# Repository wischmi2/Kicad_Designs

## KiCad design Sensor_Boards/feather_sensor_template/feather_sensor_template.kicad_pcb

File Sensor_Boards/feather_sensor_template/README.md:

# Feather sensor board template

KiCad 10 template for sensor boards that stack under the nRF54L15 feather. Each node is one feather plus one sensor board in its own enclosure (pH node, salinity node, ...). The two boards are joined by a 14-way 0.5 mm FFC between the two CN1 connectors; the R_ID resistor on the sensor board tells the firmware which board is fitted.

Derived from nrf54l15_feather_sens1 (pH) on 2026-10-25. Current numbers and open questions: STATUS.md.

## What is in the template

| Sheet | Contents | Change per board? |
|---|---|---|
| Sensor Connector | CN1 Molex 503480-1400, C1 1 uF + C2 100 nF on VSENS, R1 = R_ID (SENS_ID to GND) | Only R1's value |
| Isolation | U3 ADuM1250 I2C isolator, U4 NXE1S0303MC isolated DC-DC, C3, C4, R3/R4 4.7k isolated-side pull-ups, J5 INT_ISO test pad | Normally no. Delete it for a non-isolated board |
| Sensor | Empty. Hierarchical labels VDD_ISO, GND_ISO, SDA_ISO, SCL_ISO, INT_ISO | Yes, the sensor circuit goes here |

PCB (origin = outline top-left corner at (90, 110), the same as the feather):
- Outline 50.8 x 22.86 mm, R2.54 corners, 4 layers, same stackup, design rules and net classes as sens1.
- CN1 at (138.475, 121.43), rotation 90, pin 1 at (137.15, 124.68): exactly under the feather's CN1.
- Isolation barrier at x = 124: isolated pours (GND_ISO) end at x 122.5, host pours (GND) start at x 125.5, rule area ISOLATION_BARRIER in between on all 4 layers.
- Sensor placement area: x 90 to about 116 (isolated side), outlined on Dwgs.User. GND_ISO pours already on all 4 layers.
- Antenna-corner keep-out ANTENNA_CORNER_keepout: x 132.15 to 140.8, y 126.40 to 132.86, all copper layers, no tracks, vias or pours. It is the feather's antenna keep-out copied 1:1; the feather's chip antenna sits right above it.
- Holes at the Feather positions, 2.7 mm drill: H1 (92.54, 112.54) and H2 (92.54, 130.32) NPTH with 3.5 mm keep-outs (isolated end); H3 (138.26, 112.54) plated GND; H4 (138.26, 130.32) NPTH (inside the antenna keep-out).

## Starting a new sensor board

1. **Copy the project.** Open feather_sensor_template.kicad_pro in the KiCad project manager and use File > Save As to a new folder under Sensor_Boards (for example Sensor_Boards\feather_sens2_salinity\feather_sens2_salinity). KiCad renames the project files and keeps the sheet instances working.
   - Fallback by hand: copy the folder (skip any `~*.lck` files), rename the four `feather_sensor_template.kicad_*` files to the new name, and replace the project name inside them: `sed -i 's/"feather_sensor_template"/"<new_name>"/g' *.kicad_sch *.kicad_pro`. The footprint library nickname `feather_sensor_template` (fp-lib-table and the .pretty folder) can stay as it is.
   - Never edit the template itself for a real board.
2. **Set R_ID.** Pick the next free board type in the ID table (v4-sensor-connector.md, "Board ID - pin 11"; the R1 value field says "set per SENSORS.md", the ID register) and set R1's value to it on the Sensor Connector sheet, 1 % tolerance. Update the "SENSOR TYPE / R_ID" text on B.SilkS and record the assignment in the ID table.
3. **Fill the Sensor sheet.** Draw the sensor circuit on sensor.kicad_sch and connect it to the hierarchical labels. Delete the short wire stubs on the labels as you wire them (they only exist so the empty template passes ERC). Place new symbols in the KiCad GUI.
4. **Update the PCB** (Tools > Update PCB from Schematic), place the new parts in the sensor area, put the probe connector on the x = 90 short edge (opposite CN1, so the probe cable leaves the other end of the enclosure), route, refill the zones.
5. **Rename the board.** Title blocks on all sheets, "FEATHER SENSOR <NAME> rev" on B.SilkS, and a STATUS.md for the new board.
6. **Check.** `kicad-cli sch erc` (0 errors) and `kicad-cli pcb drc --schematic-parity --refill-zones` (0 errors, 0 unconnected, 0 parity). Export a STEP to C:\Personal-Agents\shared\handoff\<project>\ for the enclosure.

## Fixed: do not move or change

- **Outline, hole positions and origin.** The boards stack 1:1 on shared standoffs.
- **CN1**: footprint, position (138.475, 121.43), rotation 90 and pinout. Moving it breaks the straight FFC fold and the pin-1-to-pin-1 mapping.
- **Antenna-corner keep-out** under the feather's chip antenna: no copper of any kind there (no pours, tracks, vias, and no parts).
- **H1/H2 NPTH keep-outs** on an isolated board: no copper within 3.5 mm of those holes.
- **Barrier**: nothing crosses x 122.5 to 125.5 on any layer except the isolator and DC-DC packages themselves.
- All parts on the top side. The bottom stays flat (silk only), because it faces nothing and the stack height is set by the tallest top-side part.

## Sensor-board rules (from v4-sensor-connector.md)

1. Pin 1 at the same end on every board; print the FFC type on the silkscreen. For the U-folded cable the contacts end up on opposite faces at the two ends (opposite-side FFC); the 503480 is dual contact, so a same-side cable also works.
2. No I2C pull-ups on the host side of the sensor board. The feather has 4.7k to VSENS on SDA/SCL and 10k on CS and INT. (The isolated side needs its own: R3/R4 in the template.)
3. Fit the ID resistor (pin 11 to GND), 1 %.
4. Run logic from VSENS (switched 3.0 V, 100 mA max, shared with the feather's BUCK2). Use VBAT (pin 13) only for loads VSENS can't carry, behind a local regulator with an enable and sub-uA shutdown.
5. An analog output on pin 10 (AIN) must be buffered and stay within 0 to 3.0 V. It cannot cross the isolation barrier without extra parts.
6. INT (pin 9) is open-drain, active low.
7. All signals are 3.0 V logic. Before VSENS is switched off, firmware sets every CN1 signal to input or low so nothing back-powers the sensor.
8. Pin usage: I2C on 3/4; SPI on 5 to 8; UART on 6/7; SPI and UART can't be combined (shared instance). Leave unused CN1 pins unconnected.

## Isolated (default) vs non-isolated

**Isolated** (Atlas-style probes in a shared tank: pH, ORP, conductivity, DO). Keep the Isolation sheet. The sensor uses VDD_ISO / GND_ISO / SDA_ISO / SCL_ISO only, and the probe connector shell goes to GND_ISO, never host GND.
- INT_ISO only reaches the J5 test pad: the ADuM1250 has two channels (SDA, SCL). For a host interrupt use a 3-channel isolator or poll.
- VDD_ISO is the unregulated NXE1S0303MC output fed from VSENS (about 3.0 to 3.3 V, and it shares the 100 mA VSENS budget). Check it against the sensor's supply range and current. A sensor that needs a regulated or higher rail (for example EZO-EC, 3.3 V min) needs a different isolated supply, such as the VBAT-fed SN6505 + transformer + LDO in sensor-board-conductivity.md.
- Conformal-coat the isolated side; salt air across the gap defeats the isolation.
- **Nylon standoffs and screws at the isolated end (H1/H2) are mandatory.** The feather's H1/H2 (USB end) are plated and tied to feather GND and sit directly above this board's isolated end; metal hardware there would connect feather GND to the probe side. H4 is nylon too (antenna corner). H3 can be metal.

**Non-isolated** (sealed digital sensors that don't touch the water: temperature/humidity, light, pressure, sealed 1-Wire probes):
1. Delete the Isolation sheet (U3, U4, C3, C4, R3, R4, J5) from the root schematic.
2. On the root sheet, change the five global labels on the Sensor sheet pins to the host nets: VDD_ISO to VSENS, GND_ISO to GND, SDA_ISO to SENS_SDA, SCL_ISO to SENS_SCL, INT_ISO to SENS_INT (or rename the hierarchical labels). Keep C1, C2 and R1.
3. Do not add I2C pull-ups (the host has them).
4. On the PCB: delete the ISOLATION_BARRIER rule area and the GND_ISO zones, and stretch the GND zones over the whole board (keep the antenna-corner keep-out). The H1/H2 NPTH keep-outs can go; H1/H2 can be made plated GND if the board needs the extra ground.
5. Remove "ISOLATED SIDE: NYLON STANDOFFS ONLY" from B.SilkS.

## Files

- feather_sensor_template.kicad_pro / .kicad_sch / .kicad_pcb: project, root sheet, board.
- sensor_connector.kicad_sch, isolation.kicad_sch, sensor.kicad_sch: sub-sheets.
- feather_sensor_template.pretty: CN1 footprint (Molex_503480-1400_1x14-1MP_P0.50mm_Horizontal). 5034801400_0.stp: its 3D model (${KIPRJMOD}).
- The EasyEDA passives use the easyeda2kicad library, which isn't registered on this PC yet (library warnings in ERC/DRC, and no 3D bodies for them in STEP exports).

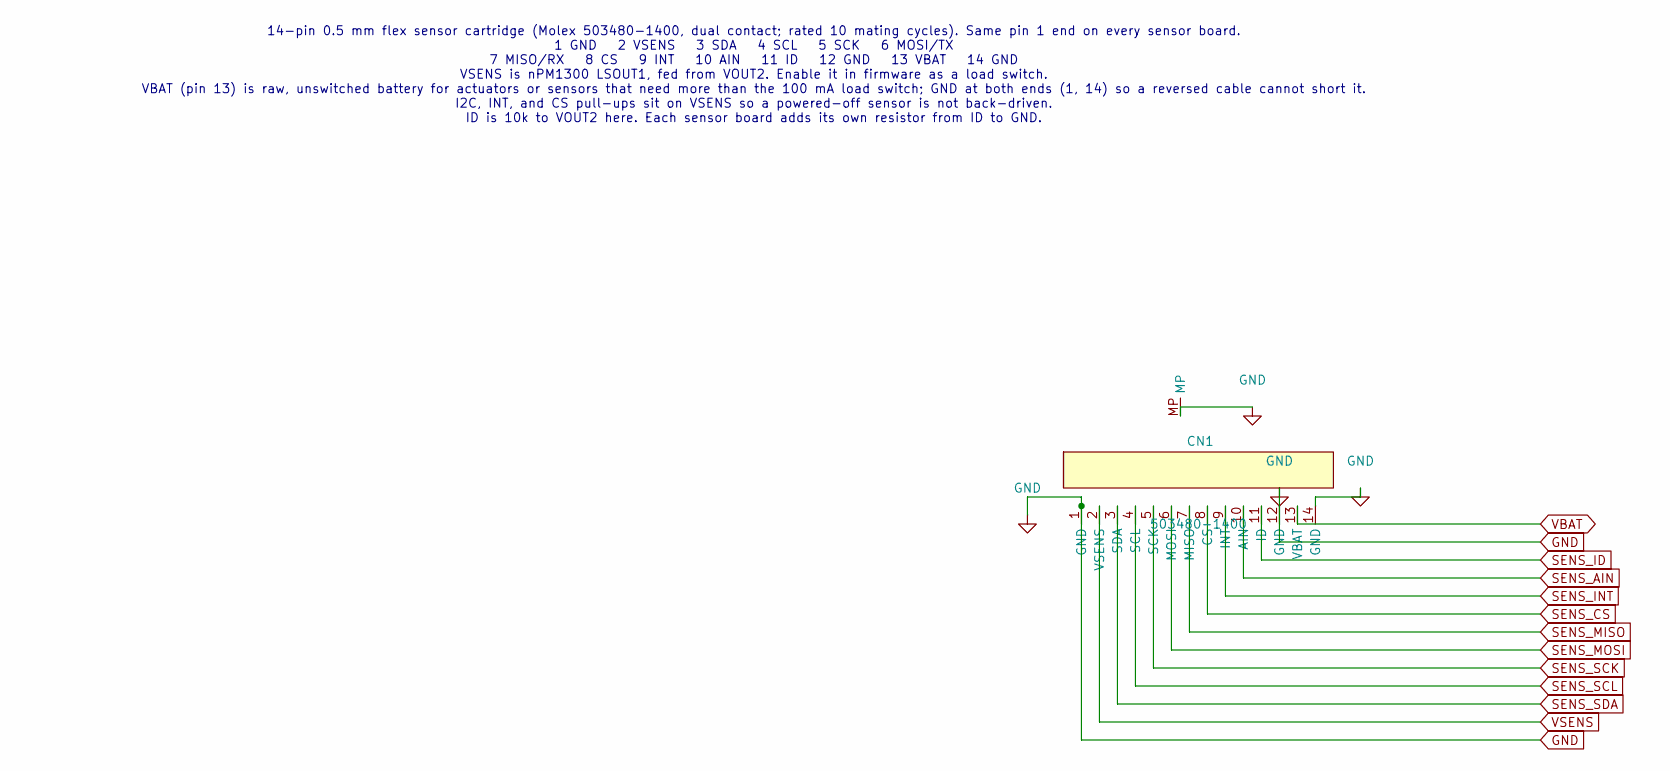
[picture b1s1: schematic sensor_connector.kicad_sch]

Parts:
CN1: 503480-1400; Molex_503480-1400_1x14-1MP_P0.50mm_Horizontal; MPN 503480-1400

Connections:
GND: CN1.1 (GND), CN1.12 (GND), CN1.14 (GND), CN1.MP; also elsewhere on the board
SENS_AIN: CN1.10 (AIN)
SENS_CS: CN1.8 (CS)
SENS_ID: CN1.11 (ID); also elsewhere on the board
SENS_INT: CN1.9 (INT)
SENS_MISO: CN1.7 (MISO)
SENS_MOSI: CN1.6 (MOSI)
SENS_SCK: CN1.5 (SCK)
SENS_SCL: CN1.4 (SCL); also elsewhere on the board
SENS_SDA: CN1.3 (SDA); also elsewhere on the board
VBAT: CN1.13 (VBAT)
VSENS: CN1.2 (VSENS); also elsewhere on the board

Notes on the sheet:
14-pin 0.5 mm flex sensor cartridge (Molex 503480-1400, dual contact; rated 10 mating cycles). Same pin 1 end on every sensor board. 1 GND 2 VSENS 3 SDA 4 SCL 5 SCK 6 MOSI/TX 7 MISO/RX 8 CS 9 INT 10 AIN 11 ID 12 GND 13 VBAT 14 GND VSENS is nPM1300 LSOUT1, fed from VOUT2. Enable it in firmware as a 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

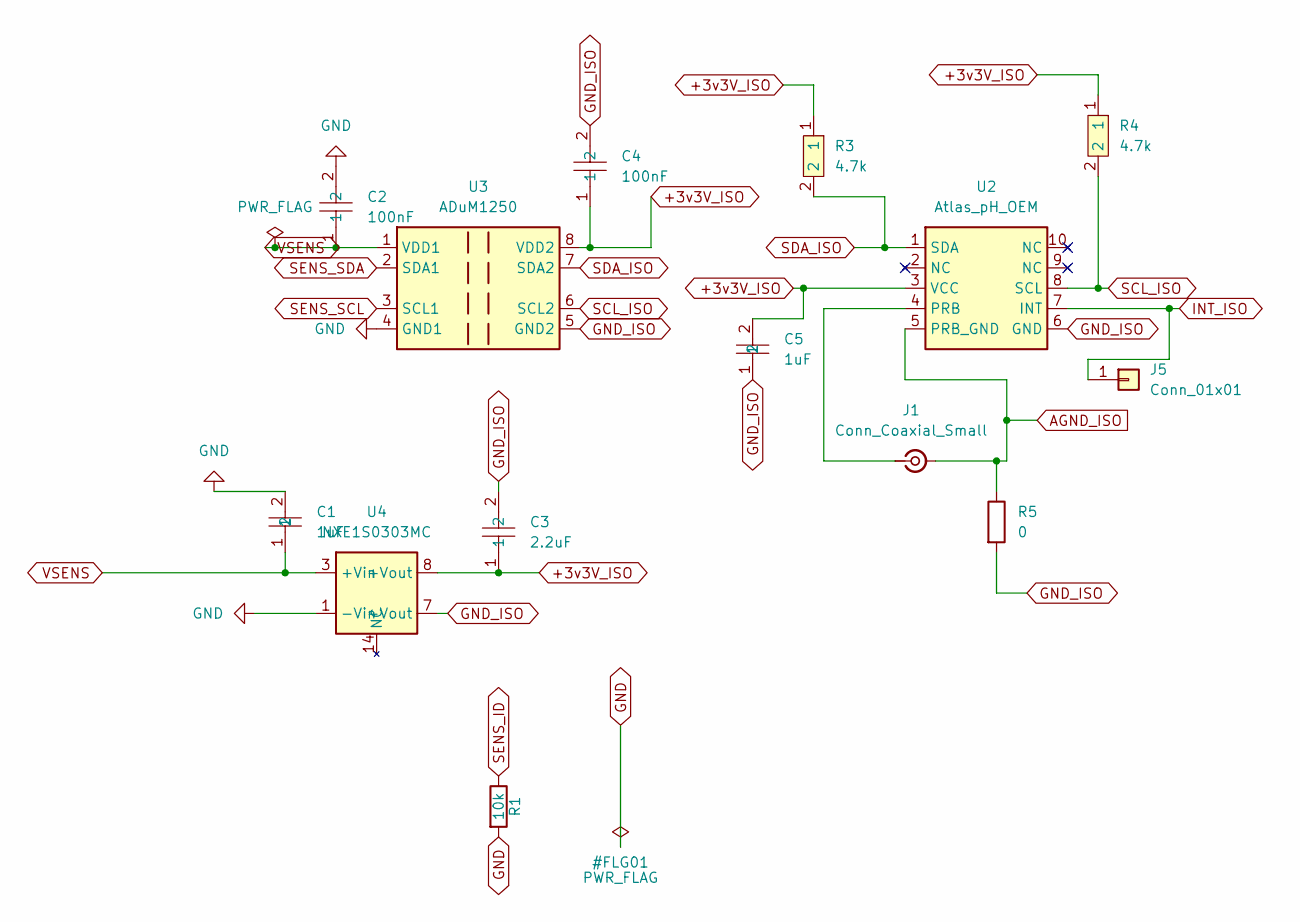
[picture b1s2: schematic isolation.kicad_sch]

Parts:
C1, C5: 1uF; C0402; MPN CL05A105KO5NNNC; LCSC Part C29266
C2, C4: 100nF; C0603; MPN CC0603KRX7R9BB104; LCSC Part C14663
C3: 2.2uF; C0603; MPN GRM188R71A225KE15D; LCSC Part C86018
J1: Conn_Coaxial_Small; SMA_BAT_Wireless_BWSMA-KWE-Z001
J5: Conn_01x01; TestPoint_Pad_D1.0mm
R1: 10k; R0402
R3, R4: 4.7k; R0402; MPN CRCW04024K70FKED; LCSC Part C482193
R5: 0; R0402
U2: Atlas_pH_OEM
U3: ADuM1250; SOIC-8_3.9x4.9mm_P1.27mm
U4: NXE1S0303MC; Converter_DCDC_Murata_NXExSxxxxMC_SMD

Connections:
+3v3V_ISO: C3.1, C4.1, C5.2, R3.1, R4.1, U2.3 (VCC), U3.8 (VDD2), U4.8 (+Vout)
AGND_ISO: J1.2 (Ext), R5.1, U2.5 (PRB_GND)
GND: C1.2, C2.2, R1.2, U3.4 (GND1), U4.1 (-Vin); also elsewhere on the board
GND_ISO: C3.2, C4.2, C5.1, R5.2, U2.6 (GND), U3.5 (GND2), U4.7 (-Vout)
INT_ISO: J5.1 (Pin_1_1), U2.7 (INT)
unnamed: J1.1 (In), U2.4 (PRB)
SCL_ISO: R4.2, U2.8 (SCL), U3.6 (SCL2)
SDA_ISO: R3.2, U2.1 (SDA), U3.7 (SDA2)
SENS_ID: R1.1; also elsewhere on the board
SENS_SCL: U3.3 (SCL1); also elsewhere on the board
SENS_SDA: U3.2 (SDA1); also elsewhere on the board
VSENS: C1.1, C2.1, U3.1 (VDD1), U4.3 (+Vin); also elsewhere on the board

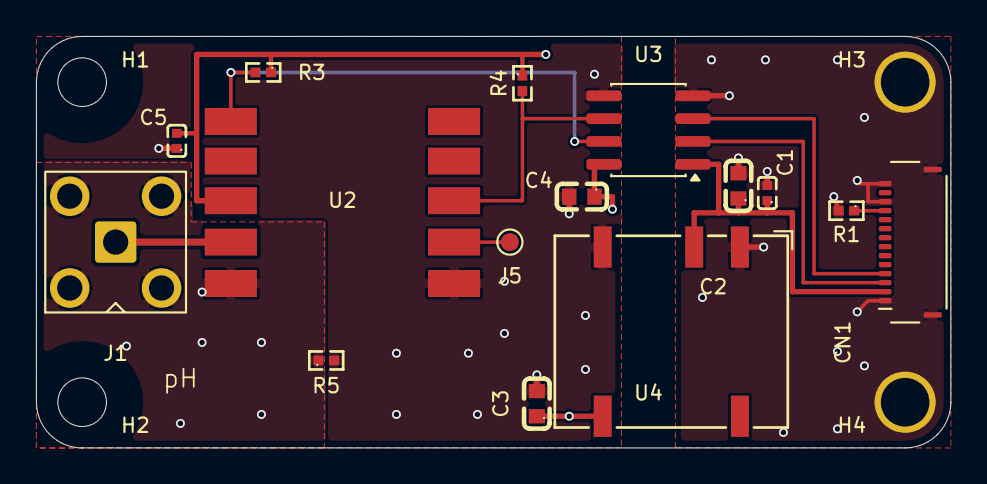
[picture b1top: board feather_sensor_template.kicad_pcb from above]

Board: 4 copper layers, 50.8 x 22.9 mm, 19 parts (0 on the bottom side), 12 nets.

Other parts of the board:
H1, H2: M2.5 2.7mm NPTH; MountingHole_2.5mm
H3, H4: M2.5 2.7mm PTH GND; MountingHole_2.5mm_Pad

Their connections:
GND: H3.1, H4.1; also elsewhere on the board

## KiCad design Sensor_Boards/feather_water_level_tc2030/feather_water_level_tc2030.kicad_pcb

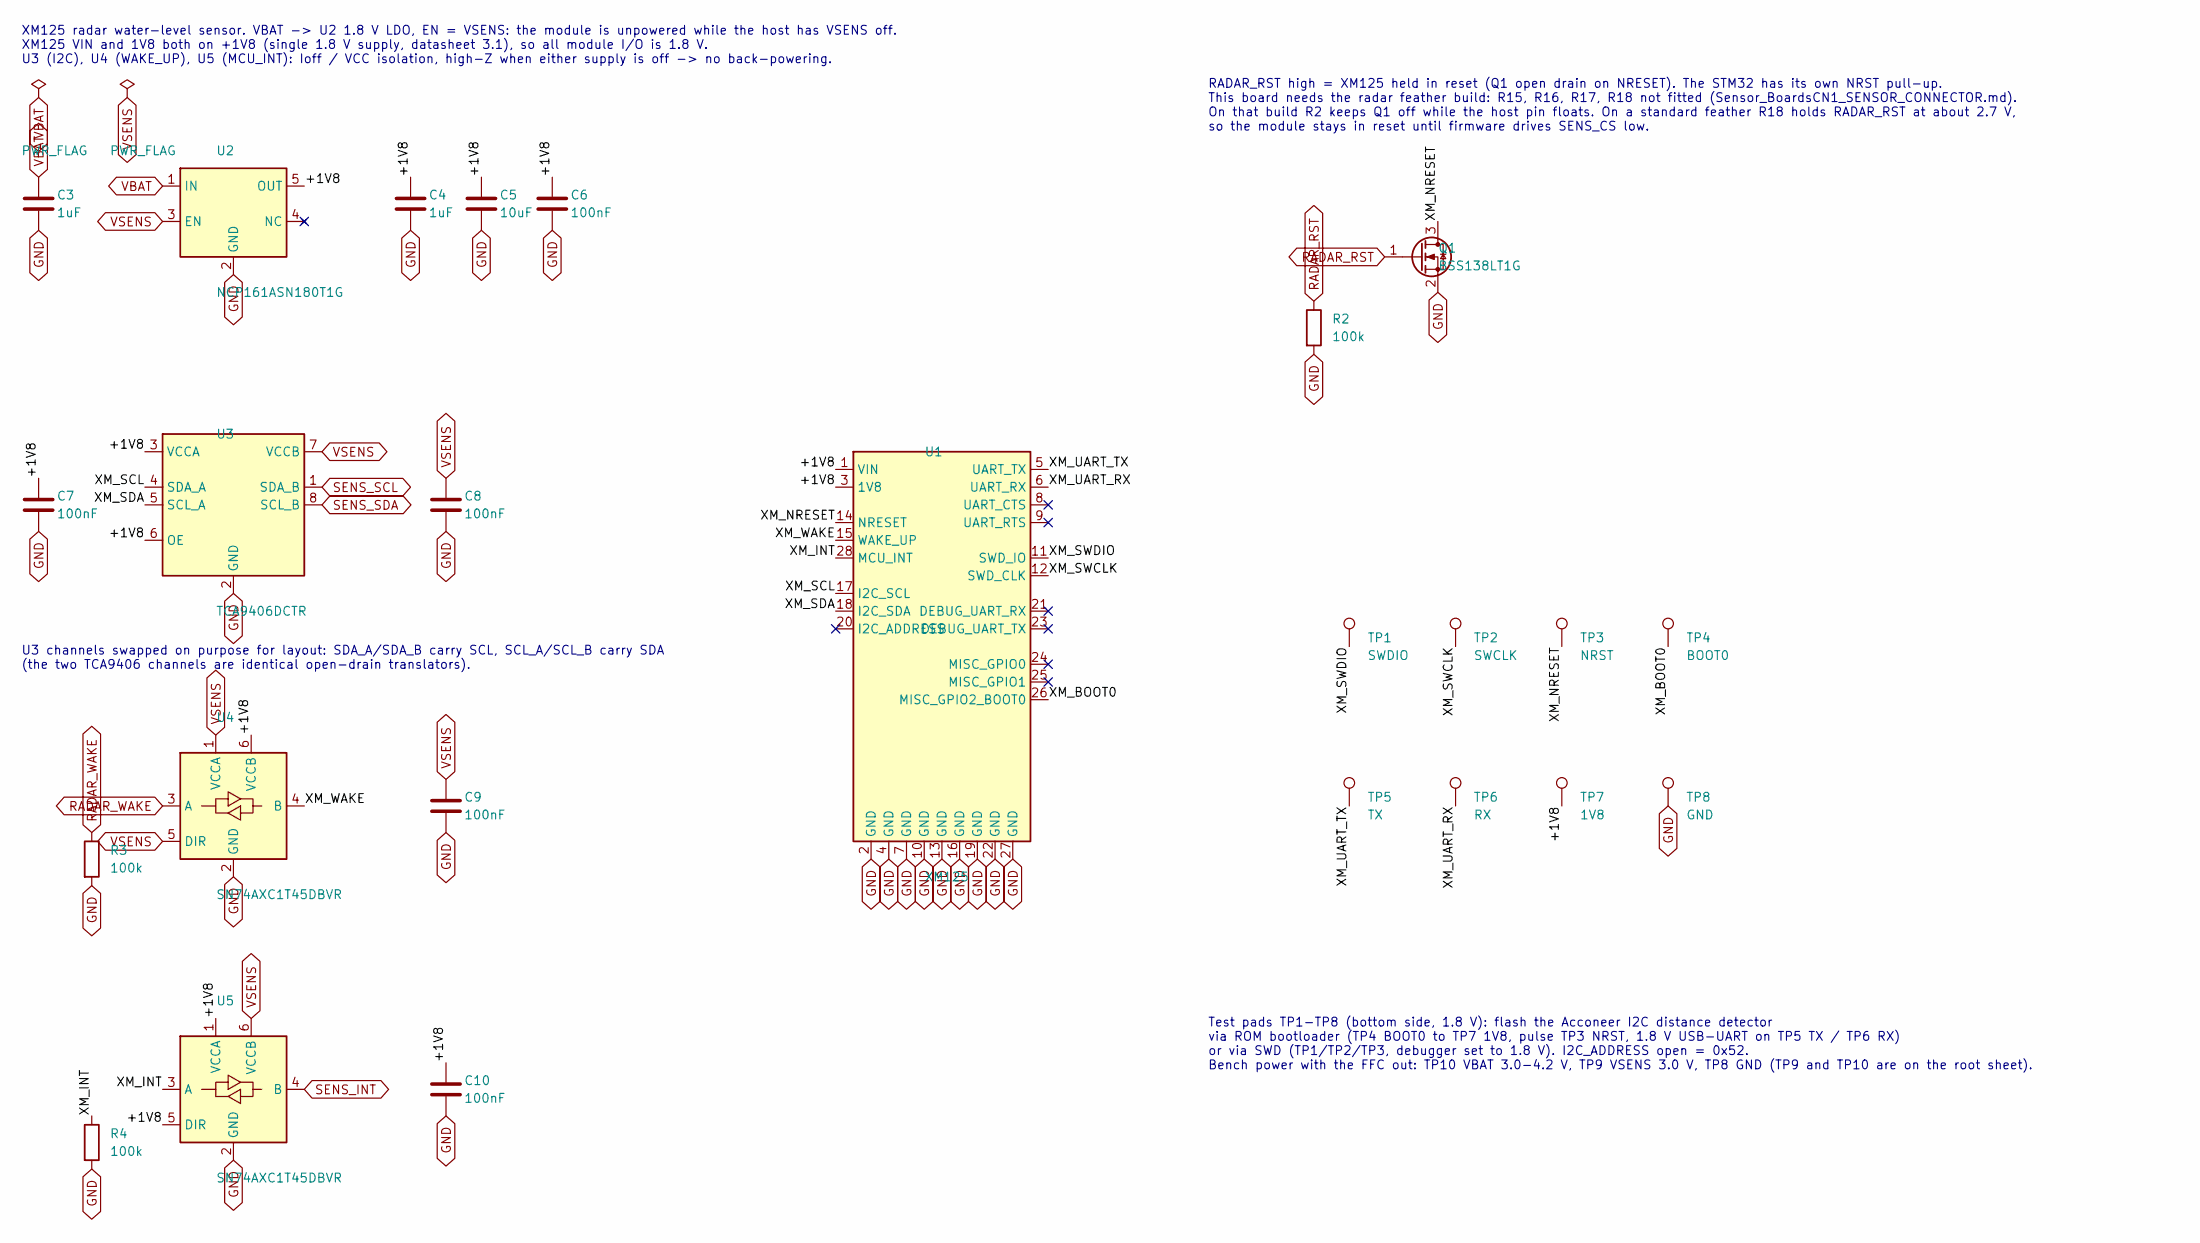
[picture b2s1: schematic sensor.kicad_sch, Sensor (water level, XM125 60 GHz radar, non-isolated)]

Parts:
C3, C4: 1uF; C_0402_1005Metric; Voltage 16V; MPN CL05A105KO5NNNC
C5: 10uF; C_0402_1005Metric; Voltage 6.3V; MPN GRM155R60J106ME15D
C6, C7, C8, C9, C10: 100nF; C_0402_1005Metric; Voltage 10V; MPN GRM155R71A104KA01D
Q1: BSS138LT1G; SOT-23; MPN BSS138LT1G
R2, R3, R4: 100k; R_0402_1005Metric; Tolerance 1%; MPN RC0402FR-07100KL
TP1: SWDIO; TestPoint_Pad_D1.0mm; MPN DNP (test pad)
TP2: SWCLK; TestPoint_Pad_D1.0mm; MPN DNP (test pad)
TP3: NRST; TestPoint_Pad_D1.0mm; MPN DNP (test pad)
TP4: BOOT0; TestPoint_Pad_D1.0mm; MPN DNP (test pad)
TP5: TX; TestPoint_Pad_D1.0mm; MPN DNP (test pad)
TP6: RX; TestPoint_Pad_D1.0mm; MPN DNP (test pad)
TP7: 1V8; TestPoint_Pad_D1.0mm; MPN DNP (test pad)
TP8: GND; TestPoint_Pad_D1.0mm; MPN DNP (test pad)
U1: XM125; Acconeer_XM125; MPN XM125
U2: NCP161ASN180T1G; SOT-23-5; MPN NCP161ASN180T1G
U3: TCA9406DCTR; SSOP-8_2.95x2.8mm_P0.65mm; MPN TCA9406DCTR
U4, U5: SN74AXC1T45DBVR; SOT-23-6; MPN SN74AXC1T45DBVR

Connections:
/Sensor/+1V8: C4.1, C5.1, C6.1, C7.1, C10.1, TP7.1, U1.1 (VIN), U1.3 (1V8), U2.5 (OUT), U3.3 (VCCA), U3.6 (OE), U4.6 (VCCB), U5.1 (VCCA), U5.5 (DIR); also elsewhere on the board
/Sensor/XM_BOOT0: TP4.1, U1.26 (MISC_GPIO2_BOOT0); also elsewhere on the board
/Sensor/XM_INT: R4.1, U1.28 (MCU_INT), U5.3 (A)
/Sensor/XM_NRESET: Q1.3 (D), TP3.1, U1.14 (NRESET); also elsewhere on the board
/Sensor/XM_SCL: U1.17 (I2C_SCL), U3.4 (SDA_A)
/Sensor/XM_SDA: U1.18 (I2C_SDA), U3.5 (SCL_A)
/Sensor/XM_SWCLK: TP2.1, U1.12 (SWD_CLK)
/Sensor/XM_SWDIO: TP1.1, U1.11 (SWD_IO)
/Sensor/XM_UART_RX: TP6.1, U1.6 (UART_RX); also elsewhere on the board
/Sensor/XM_UART_TX: TP5.1, U1.5 (UART_TX); also elsewhere on the board
/Sensor/XM_WAKE: U1.15 (WAKE_UP), U4.4 (B)
GND: C3.2, C4.2, C5.2, C6.2, C7.2, C8.2, C9.2, C10.2, Q1.2 (S), R2.2, R3.2, R4.2, TP8.1, U1.2 (GND), U1.4 (GND), U1.7 (GND), U1.10 (GND), U1.13 (GND), U1.16 (GND), U1.19 (GND), U1.22 (GND), U1.27 (GND), U2.2 (GND), U3.2 (GND), U4.2 (GND), U5.2 (GND); also elsewhere on the board
RADAR_RST: Q1.1 (G), R2.1; also elsewhere on the board
RADAR_WAKE: R3.1, U4.3 (A); also elsewhere on the board
SENS_INT: U5.4 (B); also elsewhere on the board
SENS_SCL: U3.1 (SDA_B); also elsewhere on the board
SENS_SDA: U3.8 (SCL_B); also elsewhere on the board
VBAT: C3.1, U2.1 (IN); also elsewhere on the board
VSENS: C8.1, C9.1, U2.3 (EN), U3.7 (VCCB), U4.1 (VCCA), U4.5 (DIR), U5.6 (VCCB); also elsewhere on the board

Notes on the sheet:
XM125 radar water-level sensor. VBAT -> U2 1.8 V LDO, EN = VSENS: the module is unpowered while the host has VSENS off. XM125 VIN and 1V8 both on +1V8 (single 1.8 V supply, datasheet 3.1), so all module I/O is 1.8 V. U3 (I2C), U4 (WAKE_UP), U5 (MCU_INT): Ioff / VCC isolation, high-Z when either sup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
U3 channels swapped on purpose for layout: SDA_A/SDA_B carry SCL, SCL_A/SCL_B carry SDA (the two TCA9406 channels are identical open-drain translators).
RADAR_RST high = XM125 held in reset (Q1 open drain on NRESET). The STM32 has its own NRST pull-up. This board needs the radar feather build: R15, R16, R17, R18 not fitted (Sensor_BoardsCN1_SENSOR_CONNECTOR.md). On that build R2 keeps Q1 off while the host pin floats. On a standard feather R18 hold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
Test pads TP1-TP8 (bottom side, 1.8 V): flash the Acconeer I2C distance detector via ROM bootloader (TP4 BOOT0 to TP7 1V8, pulse TP3 NRST, 1.8 V USB-UART on TP5 TX / TP6 RX) or via SWD (TP1/TP2/TP3, debugger set to 1.8 V). I2C_ADDRESS open = 0x52. Bench power with the FFC out: TP10 VBAT 3.0-4.2 V, 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

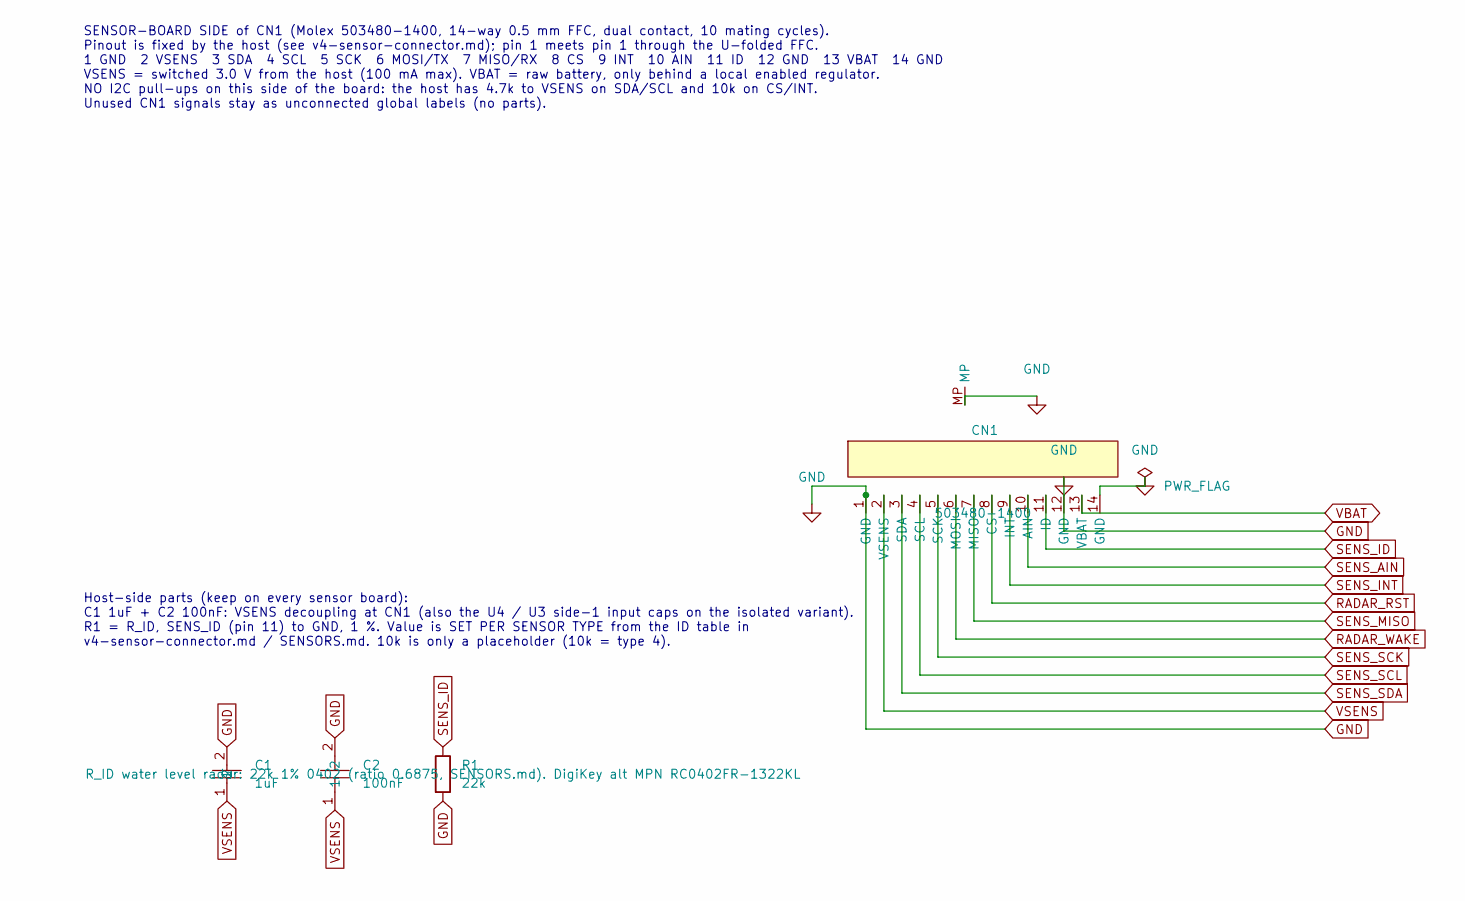
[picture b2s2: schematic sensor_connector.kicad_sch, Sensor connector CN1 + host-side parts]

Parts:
C1: 1uF; C0402; MPN CL05A105KO5NNNC; LCSC Part C29266
C2: 100nF; C0603; MPN CC0603KRX7R9BB104; LCSC Part C14663
CN1: 503480-1400; Molex_503480-1400_1x14-1MP_P0.50mm_Horizontal; MPN 503480-1400
R1: 22k; R0402; Tolerance 1%; MPN RC0402FR-0722KL

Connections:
GND: C1.2, C2.2, CN1.1 (GND), CN1.12 (GND), CN1.14 (GND), CN1.MP, R1.2; also elsewhere on the board
RADAR_RST: CN1.8 (CS); also elsewhere on the board
RADAR_WAKE: CN1.6 (MOSI); also elsewhere on the board
SENS_AIN: CN1.10 (AIN)
SENS_ID: CN1.11 (ID), R1.1
SENS_INT: CN1.9 (INT); also elsewhere on the board
SENS_MISO: CN1.7 (MISO)
SENS_SCK: CN1.5 (SCK)
SENS_SCL: CN1.4 (SCL); also elsewhere on the board
SENS_SDA: CN1.3 (SDA); also elsewhere on the board
VBAT: CN1.13 (VBAT); also elsewhere on the board
VSENS: C1.1, C2.1, CN1.2 (VSENS); also elsewhere on the board

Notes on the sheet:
SENSOR-BOARD SIDE of CN1 (Molex 503480-1400, 14-way 0.5 mm FFC, dual contact, 10 mating cycles). Pinout is fixed by the host (see v4-sensor-connector.md); pin 1 meets pin 1 through the U-folded FFC. 1 GND 2 VSENS 3 SDA 4 SCL 5 SCK 6 MOSI/TX 7 MISO/RX 8 CS 9 INT 10 AIN 11 ID 12 GND 13 VBAT 14 GND VS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
Host-side parts (keep on every sensor board): C1 1uF + C2 100nF: VSENS decoupling at CN1 (also the U4 / U3 side-1 input caps on the isolated variant). R1 = R_ID, SENS_ID (pin 11) to GND, 1 %. Value is SET PER SENSOR TYPE from the ID table in v4-sensor-connector.md / SENSORS.md. 10k is only a placeh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

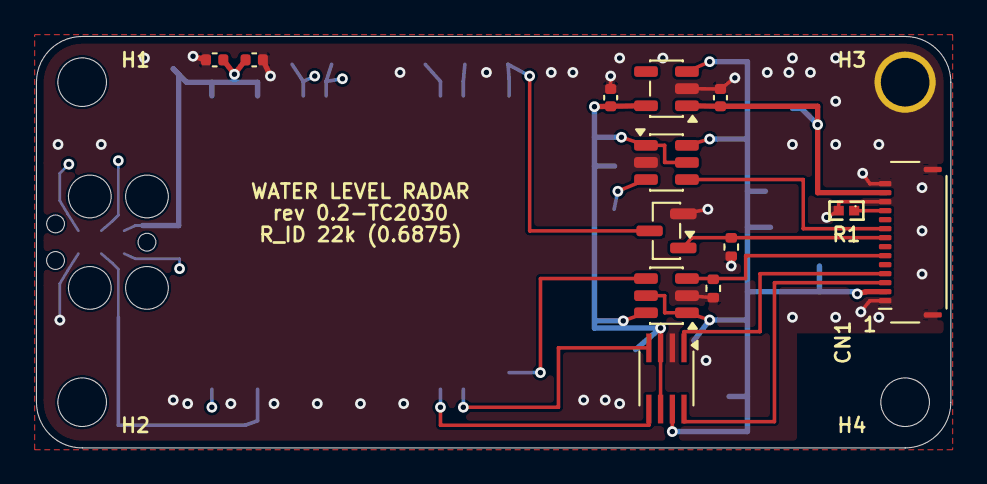
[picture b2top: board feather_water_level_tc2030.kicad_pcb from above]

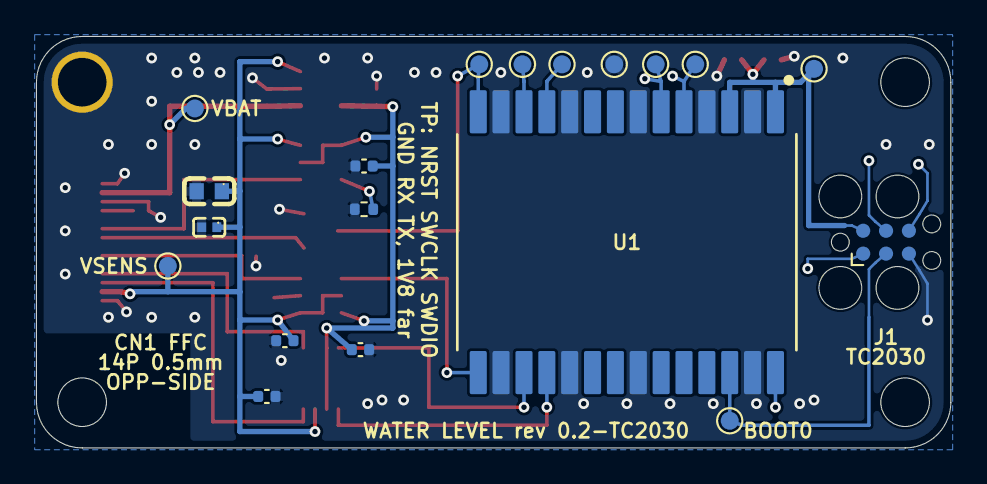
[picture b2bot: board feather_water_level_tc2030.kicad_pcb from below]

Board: 4 copper layers, 50.8 x 22.9 mm, 36 parts (19 on the bottom side), 20 nets.

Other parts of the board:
H1, H2, H4: M2.5 2.7mm NPTH; MountingHole_2.5mm
H3: M2.5 2.7mm PTH GND; MountingHole_2.5mm_Pad
J1: TC2030-IDC; Tag-Connect_TC2030-IDC-FP_2x03_P1.27mm_Vertical
TP9: VSENS; TestPoint_Pad_D1.0mm
TP10: VBAT; TestPoint_Pad_D1.0mm

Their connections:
/Sensor/+1V8: J1.2; also elsewhere on the board
/Sensor/XM_BOOT0: J1.3; also elsewhere on the board
/Sensor/XM_NRESET: J1.1; also elsewhere on the board
/Sensor/XM_UART_RX: J1.4; also elsewhere on the board
/Sensor/XM_UART_TX: J1.6; also elsewhere on the board
GND: H3.1, J1.5; also elsewhere on the board
VBAT: TP10.1; also elsewhere on the board
VSENS: TP9.1; also elsewhere on the board

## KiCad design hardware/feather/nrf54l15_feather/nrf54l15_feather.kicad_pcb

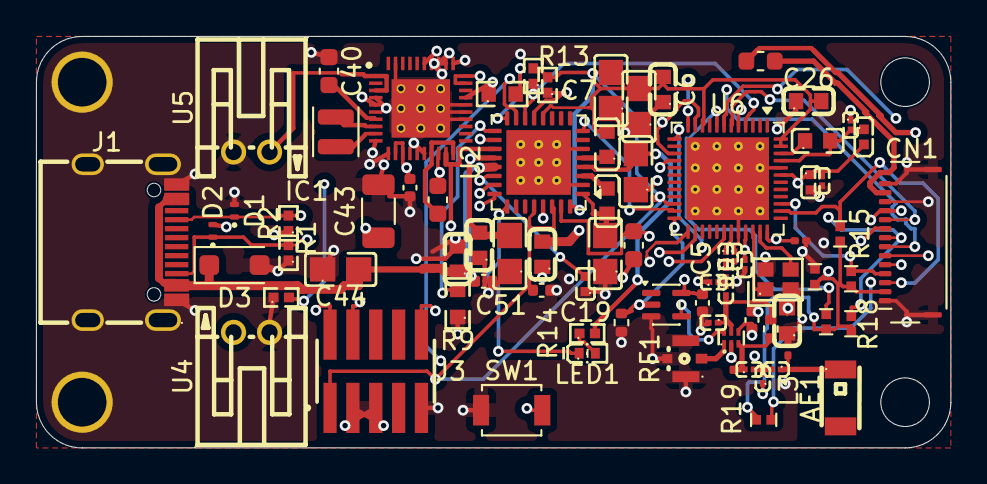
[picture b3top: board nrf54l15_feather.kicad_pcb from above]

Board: 4 copper layers, 50.8 x 22.9 mm, 83 parts (0 on the bottom side), 56 nets.

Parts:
AE1: 2450AT18A0100001E; ANT-SMD_L3.2-W1.6
C1, C10: 2.2uF; C0201
C3: 2.2uF; C0603
C5: 2.0pF; C0201
C6, C14, C15, C26: 100nF; C0603
C7, C17, C18, C20, C22: 10uF; C0805
C8: 1.5pF; C0201
C9: 10nF; C0402
C11: 2.2pF; C0201
C12: 1.0pF; C0201
C13: 0.3pF; C0201
C16: 10uF; C0603
C19: 1uF; C0402
C40: 22uF; C_0603_1608Metric
C41, C54: 10uF; C_0402_1005Metric
C42: 47uF; C_0603_1608Metric
C43: 220uF; C_1206_3216Metric
C44: 4.7uF; C0805
C45: 100nF; C0402
C46: 10uF; C_0603_1608Metric
C47: 100pF; C_0402_1005Metric
C48: 100nF; C_0402_1005Metric
C49, C50: 100nF; C_0201_0603Metric
C51: 1uF; C_0402_1005Metric
C52, C53: DNP; C_0201_0603Metric
CN1: 503480-1400; Molex_503480-1400_1x14-1MP_P0.50mm_Horizontal
D1, D2: TPD1E10B06DPYR; Texas_DPY0002A_0.6x1mm_P0.65mm
D3: SMF12A; D_SOD-123F
F1: 200mA; Fuse_0603_1608Metric
H1, H2: M2.5 plated; MountingHole_2.5mm_Pad
H3, H4: M2.5 NPTH (nylon); MountingHole_2.5mm
IC1: AEM10330-QFN; QFN40P500X500X85-41N-D
J1: TYPE-C-31-M-12; USB-C_SMD-TYPE-C-31-M-12_1
J3: FTSH-105-01-L-DV-K; SAMTEC_FTSH-105-01-L-DV-K
L2, L5: 2.7nH; L0201
L3: 3.9nH; L0201
L4: BLM15AG121SN1D; L0402
L6, L8: 3.5nH; L0201
L7: 4.7uH; L0603
L9, L10: 2.2uH; L0603
L11: 10uH; L_Sunlord_SWPA252010S
LED1: SML-P12MTT86R; LED-SMD_L1.0-W0.6-RD_SML-P12YTT86RR
R1, R2: 5.1k; R0402
R8: 10k NTC B3380; R0402
R9: 0R; R0603
R10: 150k; R0603
R11: FM8625H; DFN-6_L1.1-W0.7-P0.40-BL
R12, R13, R15, R16: 4.7k; R0402
R14: 560; R0402
R17, R18: 10k; R0402
R19: 100k; R0402
R20: 1M; R_0402_1005Metric
R21: 0R; R_0402_1005Metric
RF1: ECT818000500; ANT-SMD_ECT818000500
SW1: SW_Push; SW_SPST_B3U-1000P
U2: nPM1300-QEXX; QFN-32-1EP_5x5mm_P0.5mm_EP3.6x3.6mm_ThermalVias
U4, U5: S2B-PH-K-S; CONN-TH_S2B-PH-K-S-GW
U6: nRF54L15-QFXX; QFN-48-1EP_6x6mm_P0.4mm_EP4.6x4.6mm_ThermalVias
U7: SN74AUP1G34DCKR; SOT-353_SC-70-5
X1: XRCGB32M000F1S2AR0; CRYSTAL-SMD_4P-L2.0-W1.6-BL

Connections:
/Solar/BUFSRC: C40.1, IC1.7 (BUFSRC)
/Solar/LIN: IC1.8 (LIN), L11.1
/Solar/LOAD: C42.1, IC1.17 (LOAD), IC1.20 (EN_STO_CH)
/Solar/LOUT: IC1.9 (LOUT), L11.2
/Solar/VINT: C41.1, IC1.12 (R_MPP[1]), IC1.13 (VINT), IC1.29 (STO_PRIO), IC1.30 (T_MPP[0])
/npm1300/VSYS: C16.2, C20.2, C22.2, R14.2, U2.4 (PVDD), U2.20 (VSYS)
ANT: C13.1, L8.2, R11.5 (ANT), R21.1
ANT_CHIP: C12.1, C52.1, R11.3 (RF1), R21.2
ANT_FEED: AE1.1 (ANT_1), C53.1, L3.1
ANT_SEL: R20.1, U6.24 (P0.01), U7.2
ANT_VCTL: R11.6 (VCTL), U7.4
CC1: D1.1, J1.A5 (CC1), R2.2, U2.23 (CC1)
CC2: D2.1, J1.B5 (CC2), R1.2, U2.24 (CC2)
GND: C1.2, C3.1, C5.1, C6.1, C7.1, C8.1, C9.2, C10.1, C11.2, C13.2, C14.2, C15.1, C16.1, C17.1, C18.1, C19.1, C20.1, C22.1, C26.1, C40.2, C41.2, C42.2, C43.2, C44.1, C45.2, C46.2, C47.2, C48.2, C49.2, C50.2, C51.2, C52.2, C53.2, C54.2, CN1.1 (GND), CN1.12 (GND), CN1.14 (GND), CN1.MP, D1.2, D2.2, D3.2, H1.1, H2.1, IC1.4 (GND_1), IC1.5 (GND_2), IC1.6 (GND_3), IC1.10 (GND_4), IC1.11 (R_MPP[2]), IC1.14 (GND_5), IC1.15 (R_MPP[0]), IC1.16 (GND_6), IC1.18 (BAL), IC1.24 (LOAD_CFG[0]), IC1.25 (LOAD_CFG[1]), IC1.26 (GND_7), IC1.27 (STO_CFG[3]), IC1.28 (EN_HP), IC1.31 (EN_STO_FT), IC1.32 (T_MPP[1]), IC1.33 (STO_CFG[0]), IC1.34 (STO_CFG[1]), IC1.35 (STO_CFG[2]), IC1.39 (EN_SLEEP), IC1.41 (GROUND), J1.1 (SHIELD), J1.2 (SHIELD), J1.3 (SHIELD), J1.4 (SHIELD), J1.A1B12 (GND), J1.B1A12 (GND), J3.03, J3.05, J3.09, L2.1, R1.1, R2.1, R8.1, R9.1, R10.1, R11.2 (GND), R20.2, RF1.1 (GND), RF1.3 (GND), RF1.4 (GND), SW1.1, U2.2 (PVSS1), U2.6 (PVSS2), U2.33 (AVSS), U4.2, U5.2, U6.32 (VSS_PA), U6.44 (VSS), U6.49 (VSS), U7.3, X1.2 (GND), X1.4 (GND)
I2C_SCL: R12.1, U2.14 (SCL), U6.4 (P1.03)
I2C_SDA: R13.1, U2.13 (SDA), U6.5 (P1.04)
unnamed: C5.2, L6.2, L8.1
unnamed: C8.2, L5.2, L6.1
unnamed: C12.2, L2.2, L3.2
unnamed: LED1.2 (A), R14.1
unnamed: LED1.1 (C), U2.25 (LED0)
unnamed: R11.1 (RF2), RF1.2 (CONT)
unnamed: R8.2, U2.18 (NTC)
unnamed: SW1.2, U2.15 (SHPHLD)
unnamed: L9.1, U2.3 (SW1)
unnamed: L10.1, U2.5 (SW2)
unnamed: R9.2, U2.17 (VSET1)
unnamed: R10.2, U2.16 (VSET2)
unnamed: L5.1, U6.31 (ANT)
unnamed: L7.1, U6.46 (DCC)
unnamed: C1.1, C9.1, C11.1, L4.2, U6.33 (DECRF), U6.43 (DECA)
unnamed: C10.2, L4.1, L7.2, U6.45 (DECD)
unnamed: U6.34 (XC1), X1.1
unnamed: U6.35 (XC2), X1.3
PMIC_INT: U2.8 (GPIO1), U6.23 (P0.00)
SENS_AIN: CN1.10 (AIN), U6.6 (P1.05)
SENS_CS: CN1.8 (CS), R18.2, U6.16 (P2.05)
SENS_ID: CN1.11 (ID), R19.2, U6.7 (P1.06)
SENS_INT: CN1.9 (INT), R17.2, U6.8 (P1.07)
SENS_MISO: CN1.7 (MISO), U6.11 (P2.00), U6.15 (P2.04)
SENS_MOSI: CN1.6 (MOSI), U6.13 (P2.02)
SENS_SCK: CN1.5 (SCK), U6.12 (P2.01)
SENS_SCL: CN1.4 (SCL), R16.2, U6.39 (P1.11)
SENS_SDA: CN1.3 (SDA), R15.2, U6.38 (P1.10)
SOLAR_5p5V: IC1.1 (CS_IN), IC1.3 (SRC), U5.1
VBAT: C3.2, C43.1, F1.1, IC1.19 (STO), U2.19 (VBAT), U4.1
VBAT_CN1: CN1.13 (VBAT), F1.2
VBUS: C14.1, C44.2, C51.1, D3.1, J1.A4B9 (VBUS), J1.B4A9 (VBUS), U2.21 (VBUS)
VBUSOUT: C19.2, U2.22 (VBUSOUT)
VDDIO: C6.2, C7.2, C17.2, C26.2, C49.1, C50.1, C54.1, J3.01, L10.2, R12.2, R13.2, U2.12 (VDDIO), U2.28 (LSIN1/VINLDO1), U2.30 (LSIN2/VINLDO2), U2.32 (VOUT2), U6.10 (VDD), U6.22 (VDD), U6.36 (VDD), U6.47 (VDD), U6.48 (VDD)
VOUT1: C18.2, L9.2, U2.1 (VOUT1)
VRF: C15.2, C46.1, C47.1, C48.1, R11.4 (VDD), U2.31 (LSOUT2/VOUTLDO2), U7.5
VSENS: C45.1, CN1.2 (VSENS), R15.1, R16.1, R17.1, R18.1, R19.1, U2.29 (LSOUT1/VOUTLDO1)
nRF54_RESET: J3.10, U6.30 (~RESET)
nRF54_SWDCLK: J3.04, U6.26 (SWDCLK)
nRF54_SWDIO: J3.02, U6.25 (SWDIO)

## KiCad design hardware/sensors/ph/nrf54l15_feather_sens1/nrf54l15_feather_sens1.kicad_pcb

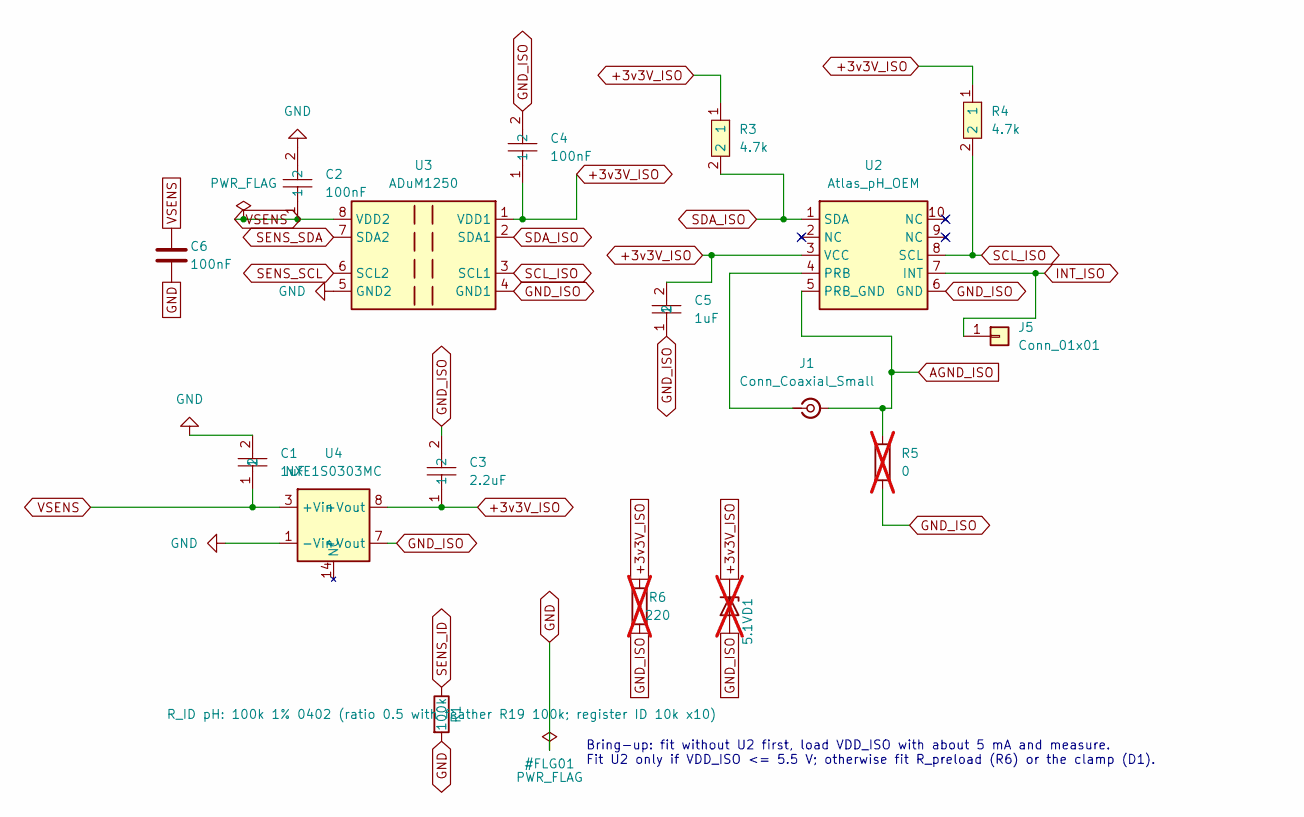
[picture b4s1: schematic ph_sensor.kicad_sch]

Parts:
C1, C5: 1uF; C0402; MPN CL05A105KO5NNNC; LCSC Part C29266
C2, C4: 100nF; C0603; MPN CC0603KRX7R9BB104; LCSC Part C14663
C3: 2.2uF; C0603; MPN GRM188R71A225KE15D; LCSC Part C86018
C6: 100nF; C_0402_1005Metric; MPN CC0402KRX7R7BB104
D1: 5.1V; D_SOD-323; MPN MM3Z5V1T1G; not fitted
J1: Conn_Coaxial_Small; SMA_BAT_Wireless_BWSMA-KWE-Z001; MPN BWSMA-KWE-Z001; LCSC Part C496551
J5: Conn_01x01; TestPoint_Pad_D1.0mm
R1: 100k; R0402; Tolerance 1%; MPN RC0402FR-07100KL
R3, R4: 4.7k; R0402; MPN CRCW04024K70FKED; LCSC Part C482193
R5: 0; R0402; MPN ERJ-2GE0R00X; not fitted
R6: 220; R_0603_1608Metric; MPN RC0603FR-07220RL; not fitted
U2: Atlas_pH_OEM; MPN OEM-pH
U3: ADuM1250; SOIC-8_3.9x4.9mm_P1.27mm; MPN ADUM1250ARZ-RL7
U4: NXE1S0303MC; Converter_DCDC_Murata_NXExSxxxxMC_SMD; MPN NXE1S0303MC-R13

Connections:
+3v3V_ISO: C3.1, C4.1, C5.2, D1.1 (K), R3.1, R4.1, R6.1, U2.3 (VCC), U3.1 (VDD1), U4.8 (+Vout)
AGND_ISO: J1.2 (Ext), R5.1, U2.5 (PRB_GND)
GND: C1.2, C2.2, C6.2, R1.2, U3.5 (GND2), U4.1 (-Vin); also elsewhere on the board
GND_ISO: C3.2, C4.2, C5.1, D1.2 (A), R5.2, R6.2, U2.6 (GND), U3.4 (GND1), U4.7 (-Vout)
INT_ISO: J5.1 (Pin_1_1), U2.7 (INT)
unnamed: J1.1 (In), U2.4 (PRB)
SCL_ISO: R4.2, U2.8 (SCL), U3.3 (SCL1)
SDA_ISO: R3.2, U2.1 (SDA), U3.2 (SDA1)
SENS_ID: R1.1; also elsewhere on the board
SENS_SCL: U3.6 (SCL2); also elsewhere on the board
SENS_SDA: U3.7 (SDA2); also elsewhere on the board
VSENS: C1.1, C2.1, C6.1, U3.8 (VDD2), U4.3 (+Vin); also elsewhere on the board

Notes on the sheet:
Bring-up: fit without U2 first, load VDD_ISO with about 5 mA and measure. Fit U2 only if VDD_ISO <= 5.5 V; otherwise fit R_preload (R6) or the clamp (D1).

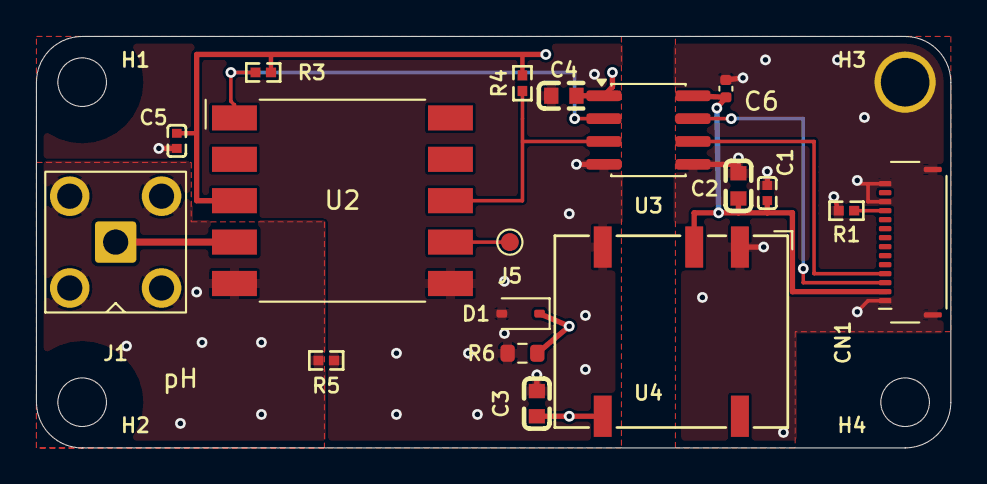
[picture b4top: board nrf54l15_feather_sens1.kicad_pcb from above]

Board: 4 copper layers, 50.8 x 22.9 mm, 22 parts (0 on the bottom side), 12 nets.

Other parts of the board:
CN1: 503480-1400; Molex_503480-1400_1x14-1MP_P0.50mm_Horizontal
H1, H2, H4: M2.5 2.7mm NPTH; MountingHole_2.5mm
H3: M2.5 2.7mm PTH GND; MountingHole_2.5mm_Pad

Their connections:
GND: CN1.1 (GND), CN1.12 (GND), CN1.14 (GND), CN1.MP, H3.1; also elsewhere on the board
SENS_ID: CN1.11 (ID); also elsewhere on the board
SENS_SCL: CN1.4 (SCL); also elsewhere on the board
SENS_SDA: CN1.3 (SDA); also elsewhere on the board
VSENS: CN1.2 (VSENS); also elsewhere on the board
